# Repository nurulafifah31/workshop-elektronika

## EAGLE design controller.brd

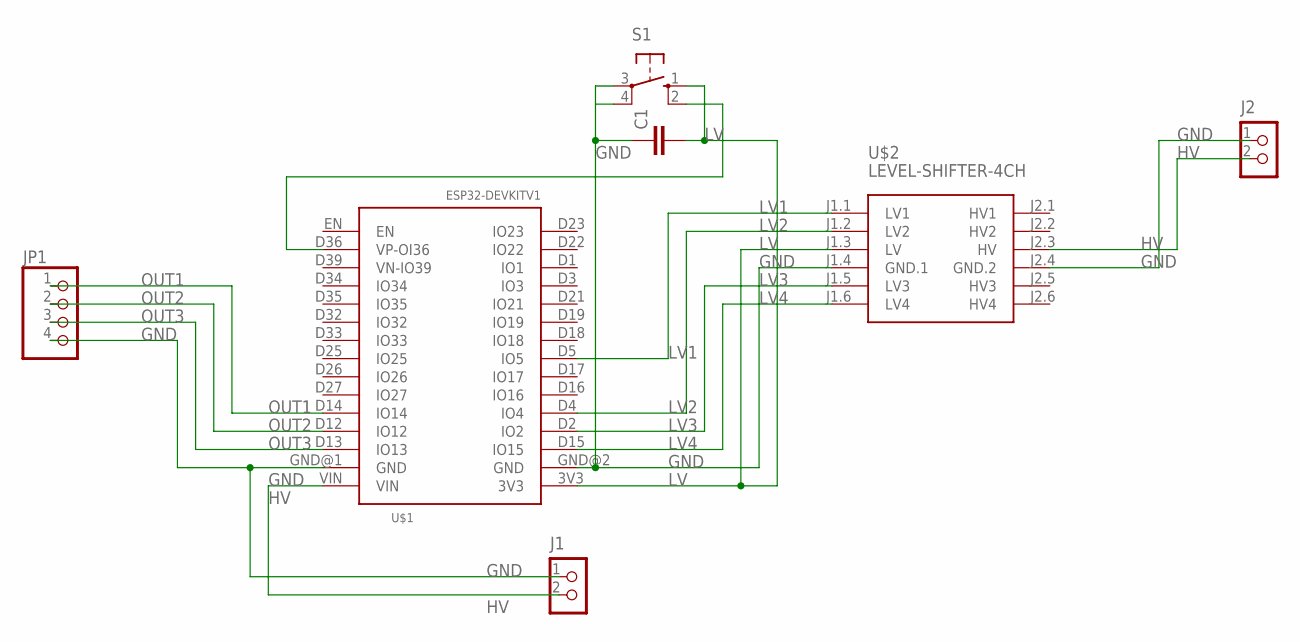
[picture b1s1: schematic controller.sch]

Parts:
C1: C-EU025-025X050; C025-025X050
J1, J2: CON_TERMINAL_BLOCK_02-5MM; TERMINAL_BLOCK_2P_5
JP1: PINHD-1X4; 1X04
S1: 10-XX; B3F-10XX
U$1: ESP32DEVKITV1; ESP32-DEVKITV1
U$2: LEVEL-SHIFTER-4CH

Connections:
GND: C1.1, J1.1, J2.1, JP1.4, S1.3, S1.4 (P1), U$1.GND@1 (GND), U$1.GND@2 (GND), U$2.J1.4 (GND.1), U$2.J2.4 (GND.2)
HV: J1.2, J2.2, U$1.VIN, U$2.J2.3 (HV)
LV: C1.2, S1.1 (S), S1.2 (S1), U$1.3V3, U$1.D36 (VP-OI36), U$2.J1.3 (LV)
LV1: U$1.D5 (IO5), U$2.J1.1 (LV1)
LV2: U$1.D4 (IO4), U$2.J1.2 (LV2)
LV3: U$1.D2 (IO2), U$2.J1.5 (LV3)
LV4: U$1.D15 (IO15), U$2.J1.6 (LV4)
OUT1: JP1.1, U$1.D14 (IO14)
OUT2: JP1.2, U$1.D12 (IO12)
OUT3: JP1.3, U$1.D13 (IO13)

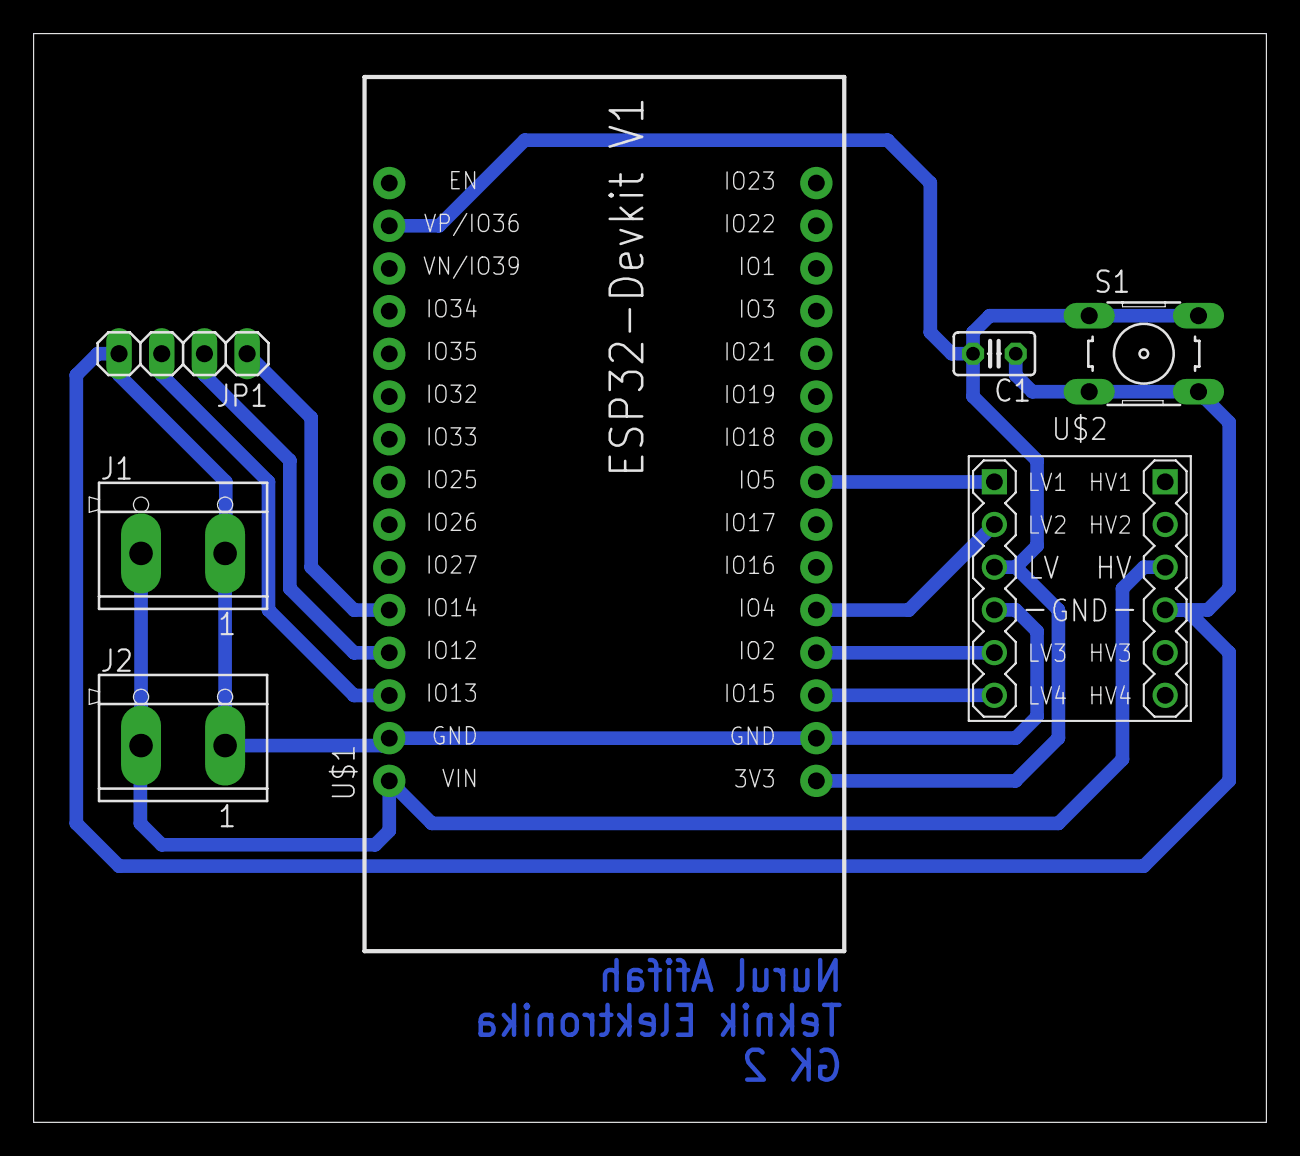
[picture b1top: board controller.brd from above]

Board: 2 copper layers, 73.3 x 64.8 mm, 7 parts (0 on the bottom side), 10 nets.

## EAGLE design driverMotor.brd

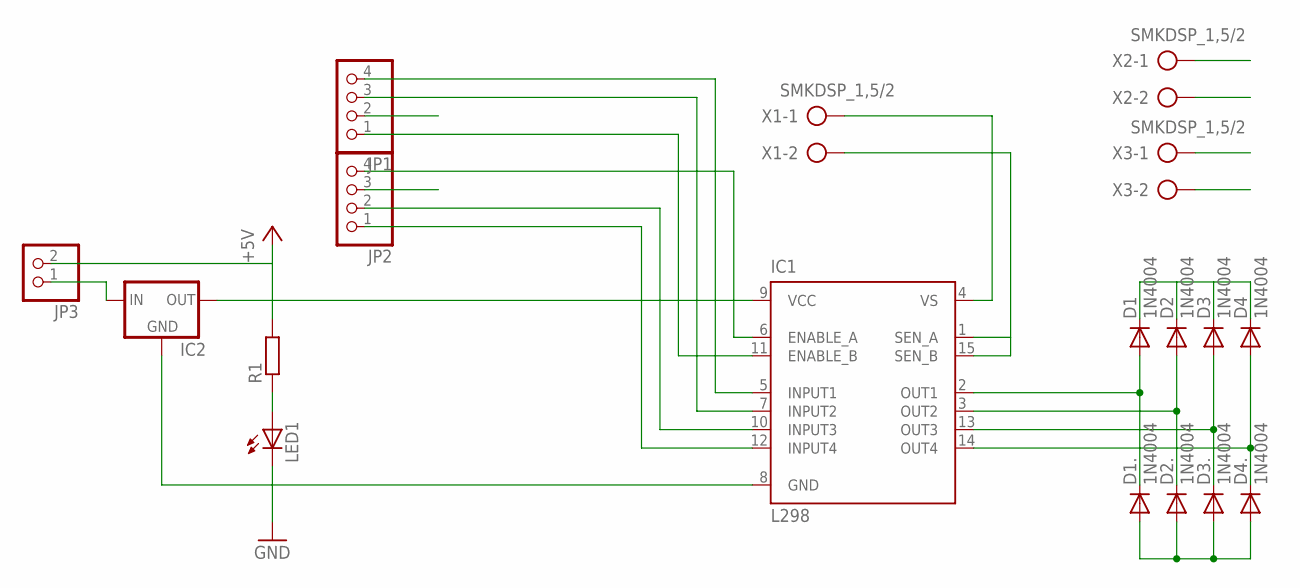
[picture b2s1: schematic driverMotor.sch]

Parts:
D1, D1., D2, D2., D3, D3., D4, D4.: 1N4004; DO41-10
IC1: L298; MULTIWATT-15
IC2: 78MXXS
JP1, JP2: PINHD-1X4; 1X04
JP3: PINHD-1X2; 1X02
LED1: LED5MM
R1: R-EU_0411/12; 0411/12
X1, X2, X3: SMKDSP_1,5/2

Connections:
+5V: IC1.9 (VCC), IC2.OUT, JP1.2, JP3.2, R1.2
ENABLE_A: IC1.6 (ENABLE_A), JP2.4
ENABLE_B: IC1.11 (ENABLE_B), JP1.1
GND: D1..A, D2..A, D3..A, D4..A, IC1.1 (SEN_A), IC1.8 (GND), IC1.15 (SEN_B), IC2.GND, JP2.3, LED1.K (C), X1.2
INPUT1: IC1.5 (INPUT1), JP1.4
INPUT2: IC1.7 (INPUT2), JP1.3
INPUT3: IC1.10 (INPUT3), JP2.2
INPUT4: IC1.12 (INPUT4), JP2.1
LED: LED1.A, R1.1
MOTOR1_1: D1.A, D1..C, IC1.2 (OUT1), X2.1
MOTOR1_2: D2.A, D2..C, IC1.3 (OUT2), X2.2
MOTOR2_1: D3.A, D3..C, IC1.13 (OUT3), X3.1
MOTOR2_2: D4.A, D4..C, IC1.14 (OUT4), X3.2
unnamed: IC2.IN, JP3.1
VS: D1.C, D2.C, D3.C, D4.C, IC1.4 (VS), X1.1

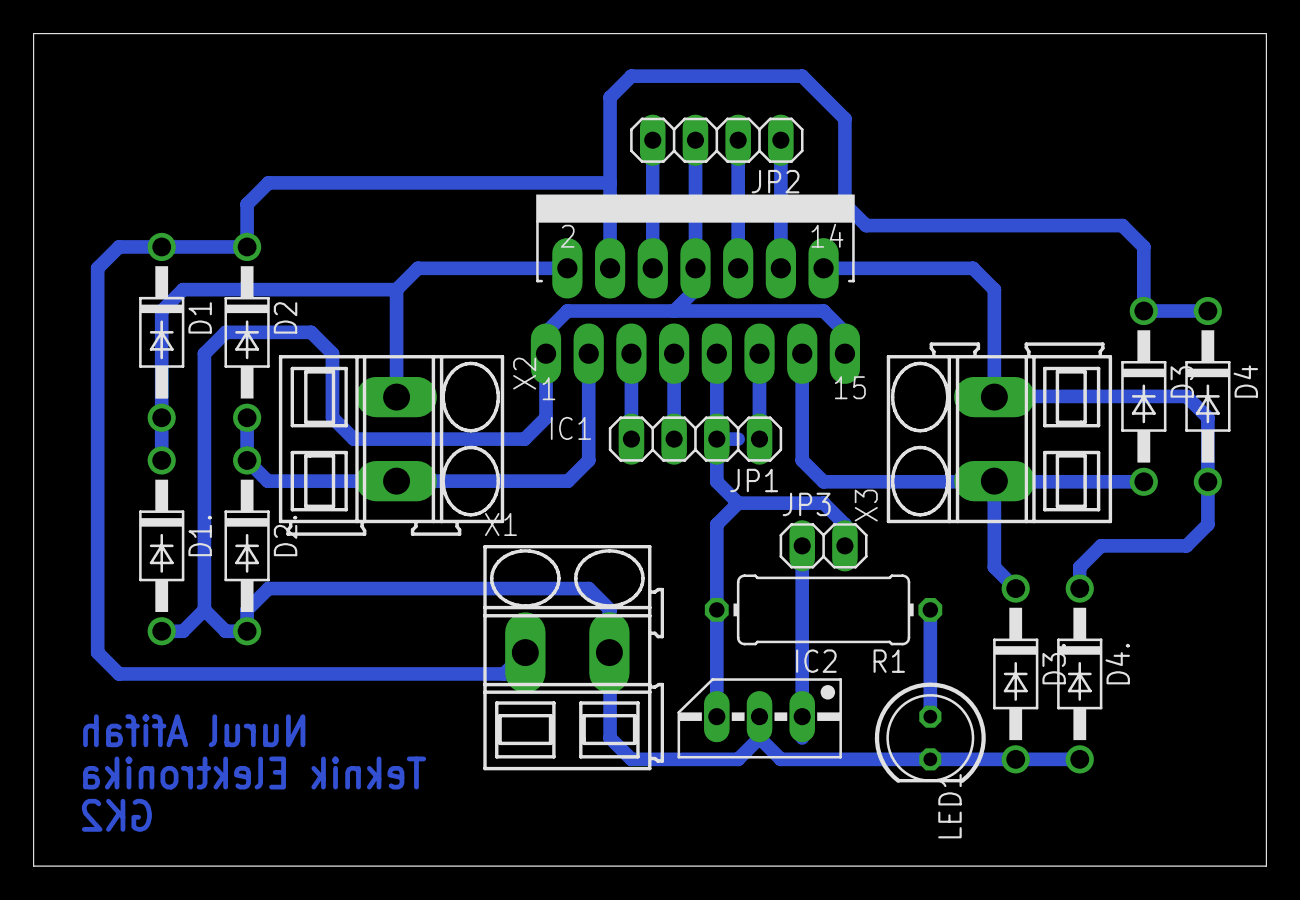
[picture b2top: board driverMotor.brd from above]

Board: 2 copper layers, 73.3 x 49.5 mm, 18 parts (0 on the bottom side), 15 nets.

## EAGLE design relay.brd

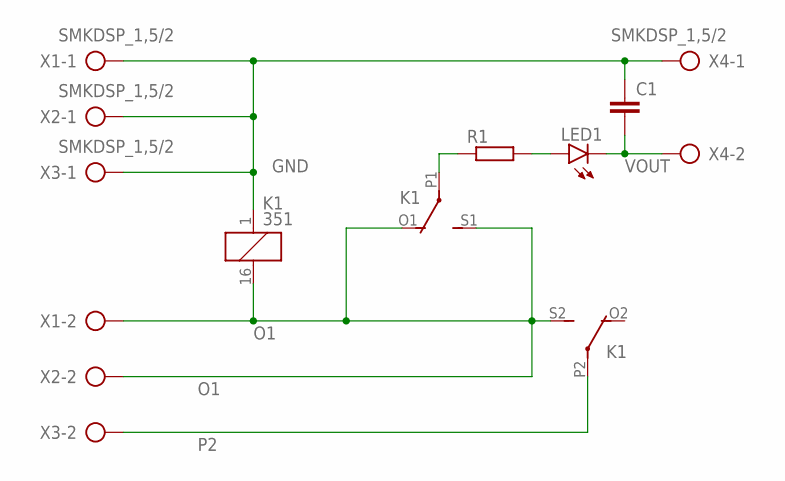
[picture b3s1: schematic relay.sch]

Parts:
C1: C-EU025-025X050; C025-025X050
K1: 351
LED1: LED3MM
R1: R-EU_0207/10; 0207/10
X1, X2, X3, X4: SMKDSP_1,5/2

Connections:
GND: C1.1, K1.1, X1.1, X2.1, X3.1, X4.1
unnamed: K1.P1, R1.1
unnamed: LED1.A, R1.2
O1: K1.16 (2), K1.O1 (O), K1.S1 (S), K1.S2 (S), X1.2, X2.2
P2: K1.P2, X3.2
VOUT: C1.2, LED1.K (C), X4.2

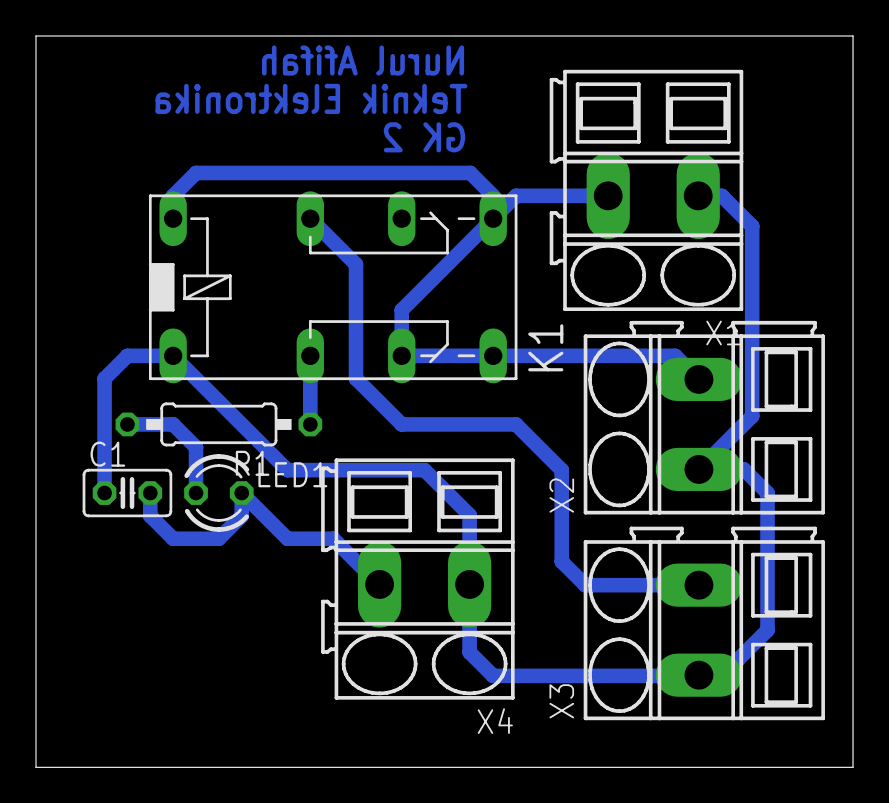
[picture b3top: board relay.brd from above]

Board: 2 copper layers, 45.4 x 40.6 mm, 8 parts (0 on the bottom side), 6 nets.

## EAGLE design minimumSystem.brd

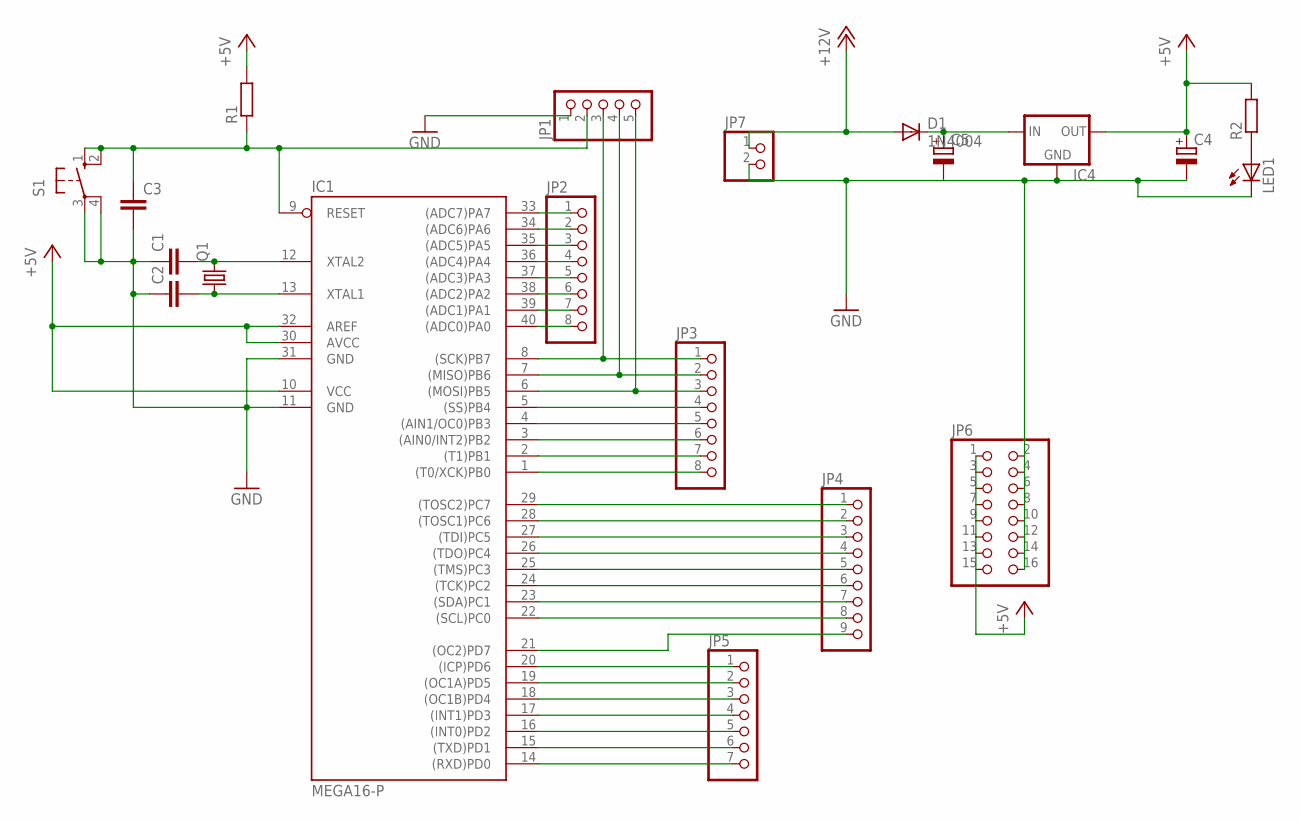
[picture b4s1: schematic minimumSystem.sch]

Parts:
C1, C2: C-EU025-024X044; C025-024X044
C3: C-EU050-025X075; C050-025X075
C4, C5: CPOL-EUE2.5-5; E2,5-5
D1: 1N4004; DO41-10
IC1: MEGA16-P; DIL40
IC4: 78XXS
JP1: PINHD-1X5; 1X05
JP2, JP3: PINHD-1X8; 1X08
JP4: PINHD-1X9; 1X09
JP5: PINHD-1X7; 1X07
JP6: PINHD-2X8; 2X08
JP7: PINHD-1X2; 1X02
LED1: LED5MM
Q1: CRYSTALHC49U-V; HC49U-V
R1, R2: R-EU_0204/7; 0204/7
S1: 10-XX; B3F-10XX

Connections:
+5V: C4.+, IC1.10 (VCC), IC1.30 (AVCC), IC1.32 (AREF), IC4.OUT, JP6.1, JP6.3, JP6.5, JP6.7, JP6.9, JP6.11, JP6.13, JP6.15, R1.2, R2.2
+12V: D1.A, JP7.1
C0: IC1.22 ((SCL)PC0), JP4.8
C1: IC1.23 ((SDA)PC1), JP4.7
C2: IC1.24 ((TCK)PC2), JP4.6
C3: IC1.25 ((TMS)PC3), JP4.5
D7: IC1.14 ((RXD)PD0), JP5.7
GND: C1.1, C2.1, C3.2, C4.-, C5.-, IC1.11 (GND), IC1.31 (GND), IC4.GND, JP1.1, JP6.2, JP6.4, JP6.6, JP6.8, JP6.10, JP6.12, JP6.14, JP6.16, JP7.2, LED1.K (C), S1.3, S1.4 (P1)
unnamed: IC1.33 ((ADC7)PA7), JP2.1
unnamed: IC1.34 ((ADC6)PA6), JP2.2
unnamed: IC1.35 ((ADC5)PA5), JP2.3
unnamed: IC1.36 ((ADC4)PA4), JP2.4
unnamed: IC1.37 ((ADC3)PA3), JP2.5
unnamed: IC1.38 ((ADC2)PA2), JP2.6
unnamed: IC1.39 ((ADC1)PA1), JP2.7
unnamed: IC1.40 ((ADC0)PA0), JP2.8
unnamed: C3.1, IC1.9 (RESET), JP1.2, R1.1, S1.1 (S), S1.2 (S1)
unnamed: IC1.29 ((TOSC2)PC7), JP4.1
unnamed: IC1.28 ((TOSC1)PC6), JP4.2
unnamed: IC1.27 ((TDI)PC5), JP4.3
unnamed: IC1.5 ((SS)PB4), JP3.4
unnamed: IC1.20 ((ICP)PD6), JP5.1
unnamed: IC1.19 ((OC1A)PD5), JP5.2
unnamed: IC1.26 ((TDO)PC4), JP4.4
unnamed: IC1.6 ((MOSI)PB5), JP1.5, JP3.3
unnamed: IC1.4 ((AIN1/OC0)PB3), JP3.5
unnamed: IC1.3 ((AIN0/INT2)PB2), JP3.6
unnamed: IC1.2 ((T1)PB1), JP3.7
unnamed: IC1.1 ((T0/XCK)PB0), JP3.8
unnamed: C5.+, D1.C, IC4.IN
unnamed: IC1.15 ((TXD)PD1), JP5.6
unnamed: IC1.16 ((INT0)PD2), JP5.5
unnamed: IC1.17 ((INT1)PD3), JP5.4
unnamed: IC1.18 ((OC1B)PD4), JP5.3
unnamed: C1.2, IC1.12 (XTAL2), Q1.2
unnamed: C2.2, IC1.13 (XTAL1), Q1.1
unnamed: LED1.A, R2.1
unnamed: IC1.8 ((SCK)PB7), JP1.3, JP3.1
unnamed: IC1.7 ((MISO)PB6), JP1.4, JP3.2
RS: IC1.21 ((OC2)PD7), JP4.9

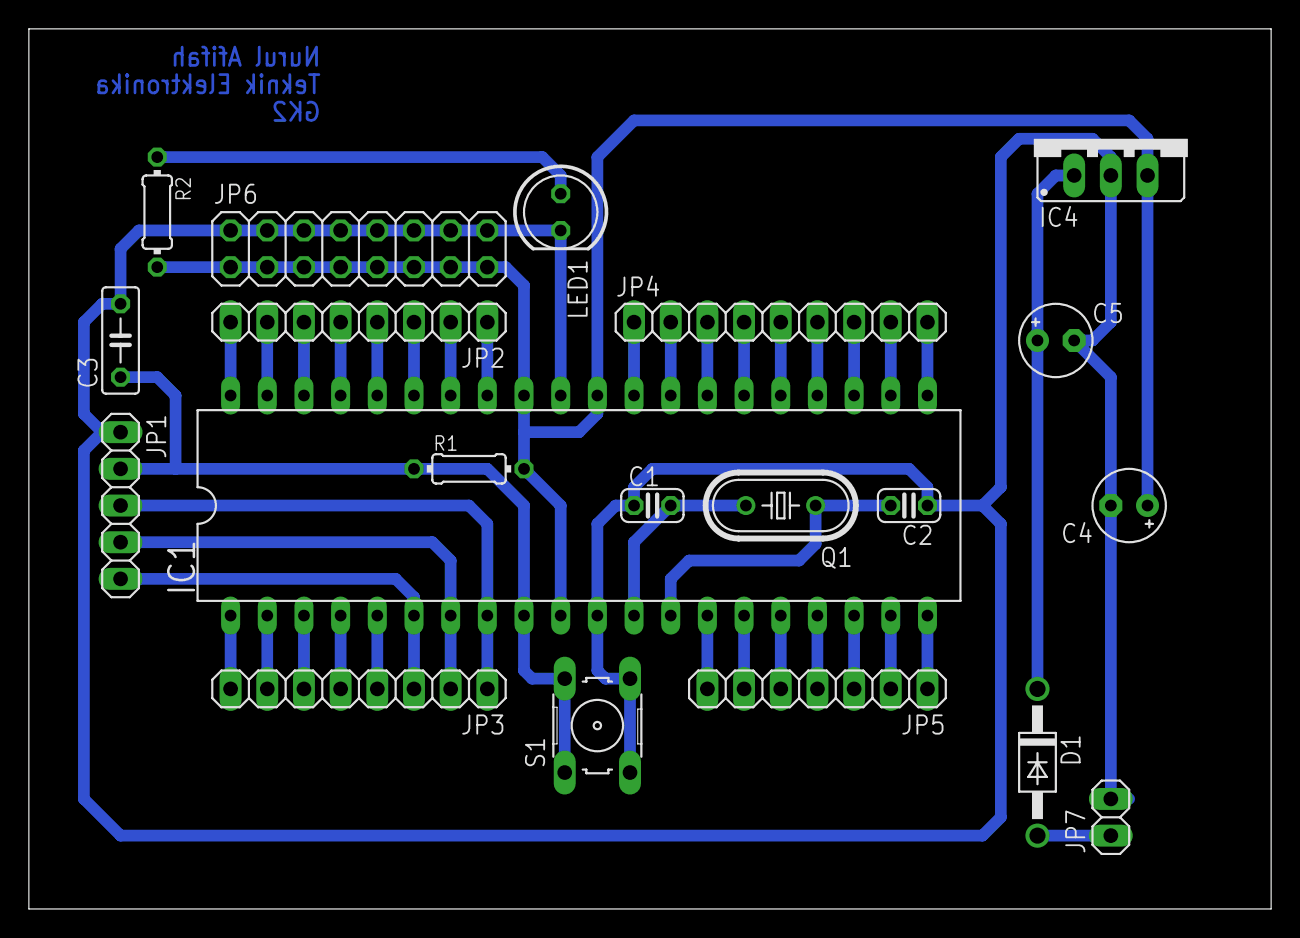
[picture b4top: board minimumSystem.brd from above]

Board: 2 copper layers, 86.0 x 61.0 mm, 20 parts (0 on the bottom side), 40 nets.

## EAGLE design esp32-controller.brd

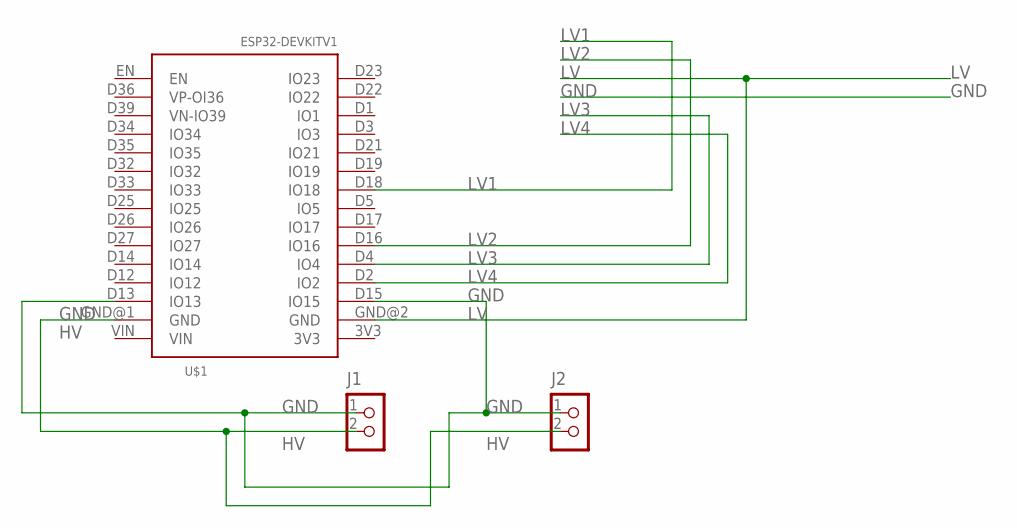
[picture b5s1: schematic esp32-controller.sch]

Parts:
J1, J2: CON_TERMINAL_BLOCK_02-5MM; TERMINAL_BLOCK_2P_5
U$1: ESP32DEVKITV1; ESP32-DEVKITV1

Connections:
GND: J1.1, J2.1, U$1.D13 (IO13), U$1.D15 (IO15)
HV: J1.2, J2.2, U$1.GND@1 (GND)
LV: U$1.GND@2 (GND)
LV1: U$1.D18 (IO18)
LV2: U$1.D16 (IO16)
LV3: U$1.D4 (IO4)
LV4: U$1.D2 (IO2)

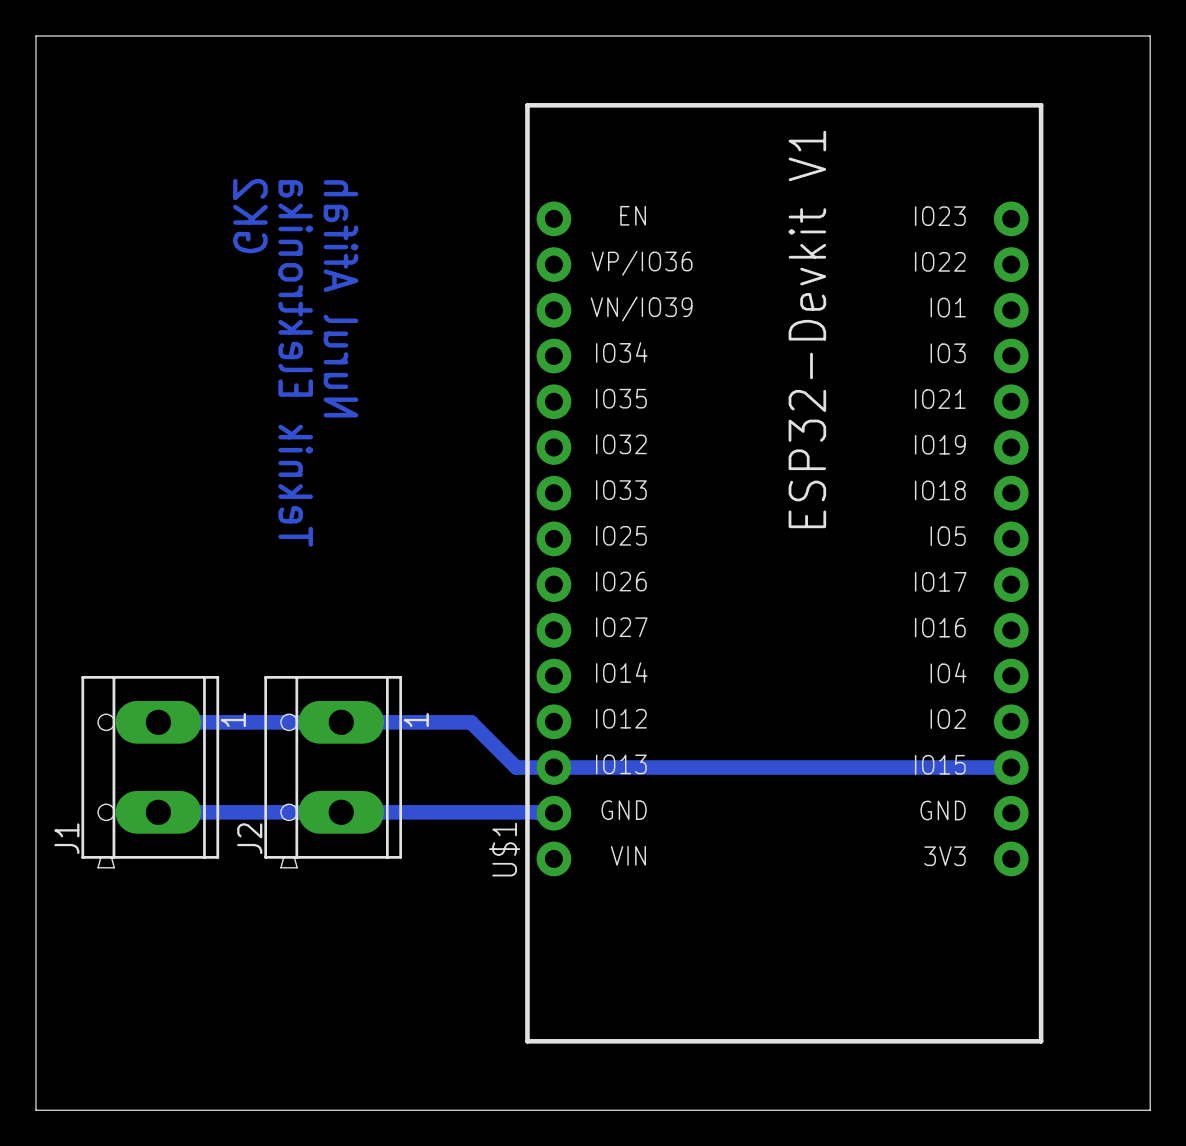
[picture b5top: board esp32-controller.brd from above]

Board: 2 copper layers, 61.9 x 59.7 mm, 3 parts (0 on the bottom side), 2 nets.

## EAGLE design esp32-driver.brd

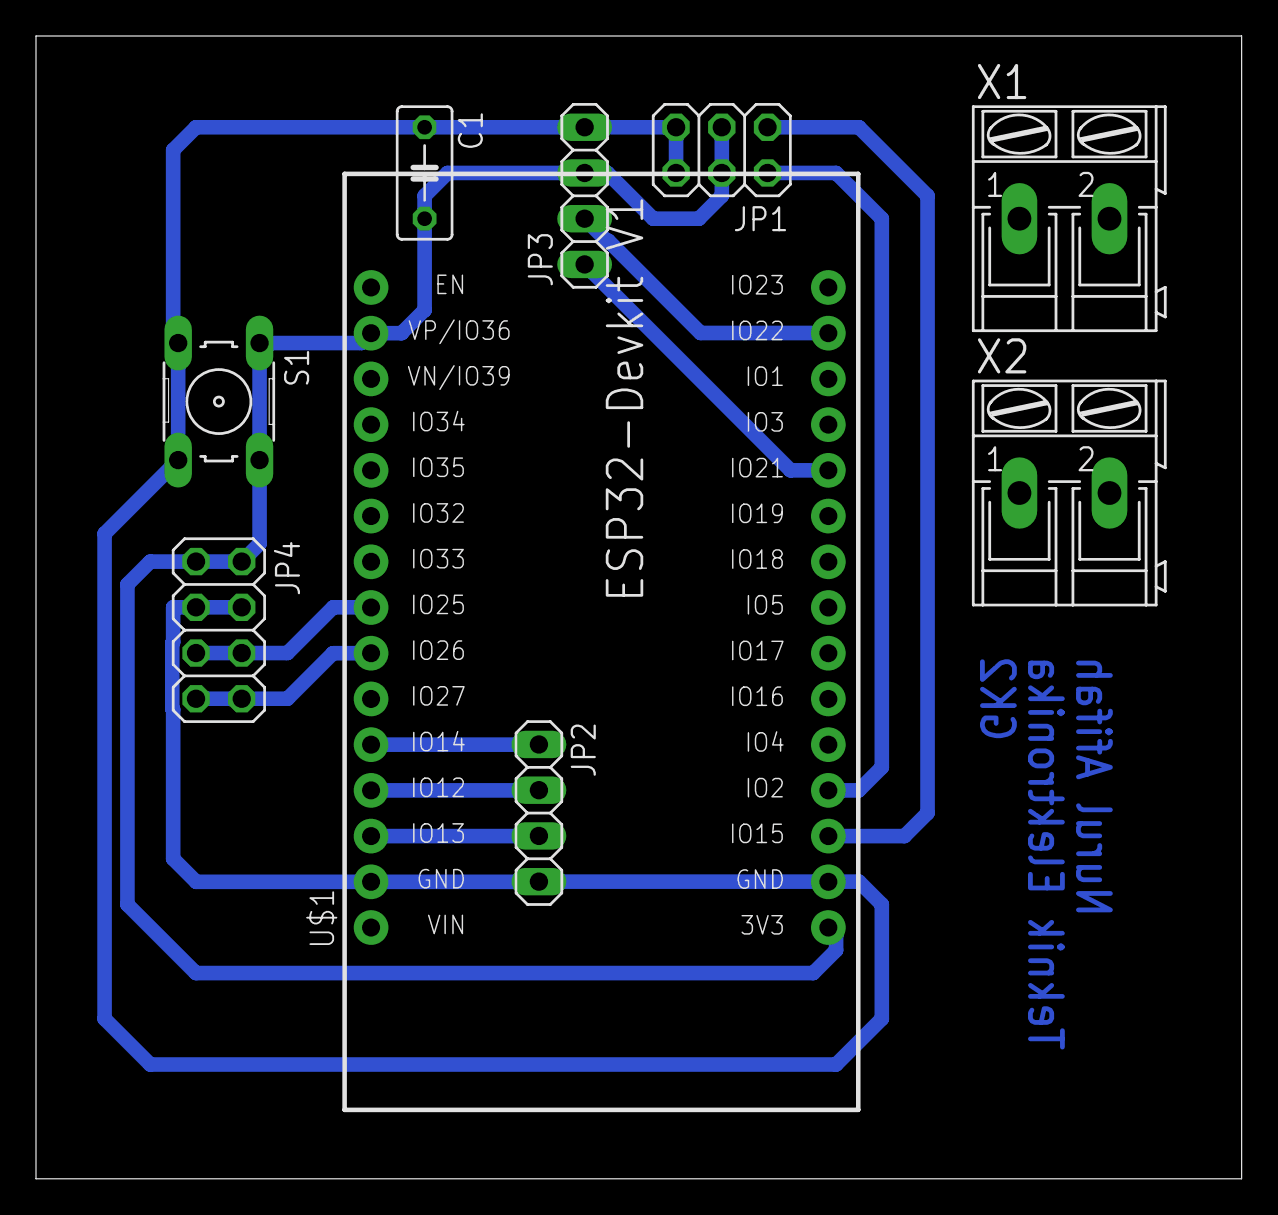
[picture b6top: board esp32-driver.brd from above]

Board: 2 copper layers, 67.0 x 63.5 mm, 9 parts (0 on the bottom side), 11 nets.

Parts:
C1: C050-030X075
JP1: 2X03
JP2, JP3: 1X04
JP4: 2X04
S1: B3F-10XX
U$1: ESP32DEVKITV1; ESP32-DEVKITV1
X1, X2: AK300/2

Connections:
GND: C1.1, JP1.5, JP1.6, JP2.4, JP3.4, JP4.3, JP4.4, S1.3, S1.4, U$1.GND@1, U$1.GND@2
MOISTURE: JP1.2, U$1.D2
OUT1: JP2.1, U$1.D14
OUT2: JP2.2, U$1.D12
OUT3: JP2.3, U$1.D13
PH: JP1.1, U$1.D15
SCL: JP3.2, U$1.D22
SCL2: JP4.5, JP4.6, U$1.D25
SDA: JP3.1, U$1.D21
SDA2: JP4.7, JP4.8, U$1.D26
V: C1.2, JP1.3, JP1.4, JP3.3, JP4.1, JP4.2, S1.1, S1.2, U$1.3V3, U$1.D36

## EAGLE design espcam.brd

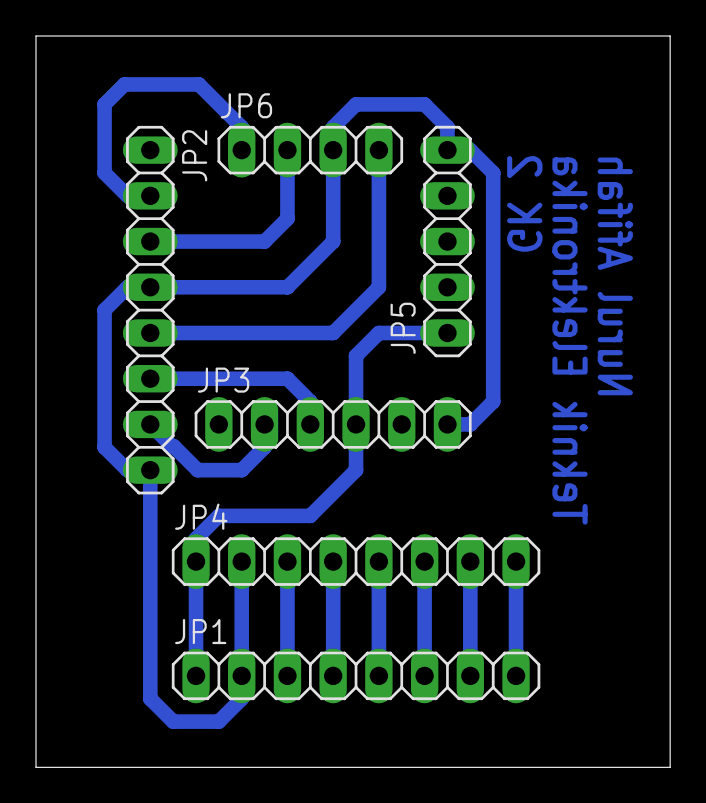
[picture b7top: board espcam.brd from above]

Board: 2 copper layers, 35.2 x 40.6 mm, 6 parts (0 on the bottom side), 13 nets.

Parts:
JP1, JP2, JP4: 1X08
JP3: 1X06
JP5: 1X05
JP6: 1X04

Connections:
5V: JP1.1, JP3.4, JP4.1, JP5.1
GND: JP1.2, JP2.4, JP2.8, JP3.6, JP4.2, JP5.5, JP6.3
IO0: JP2.3, JP6.2
IO2: JP1.7, JP4.7
IO4: JP1.8, JP4.8
IO12: JP1.3, JP4.3
IO13: JP1.4, JP4.4
IO14: JP1.6, JP4.6
IO15: JP1.5, JP4.5
IO16: JP2.2, JP6.1
RX: JP2.7, JP3.2
TX: JP2.6, JP3.3
VOUT: JP2.5, JP6.4

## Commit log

2021-11-11 Create Schematic dan Board
2021-11-11 Schematic dan Board

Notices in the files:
parts and their libraries:
diy-model: Released under the Creative Commons Attribution 4.0 International License: http://creativecommons.org/licenses/by/4.0
